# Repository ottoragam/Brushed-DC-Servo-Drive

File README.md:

# Brushed-DC-Servo-Drive
Low cost servo drive for small CNC machinery

##New version available on https://github.com/ottoragam/Tarocco

----------------------------------------------------------------------
Brushed DC Servo Drive (c) by Gino Magarotto

Brushed DC Servo Drive is licensed under a
Creative Commons Attribution-ShareAlike 3.0 Unported License.

You should have received a copy of the license along with this
work.  If not, see <http://creativecommons.org/licenses/by-sa/3.0/>.

----------------------------------------------------------------------
Low cost servo drive for small CNC machinery

Project log on https://hackaday.io/project/9433-brushed-dc-servo-drive

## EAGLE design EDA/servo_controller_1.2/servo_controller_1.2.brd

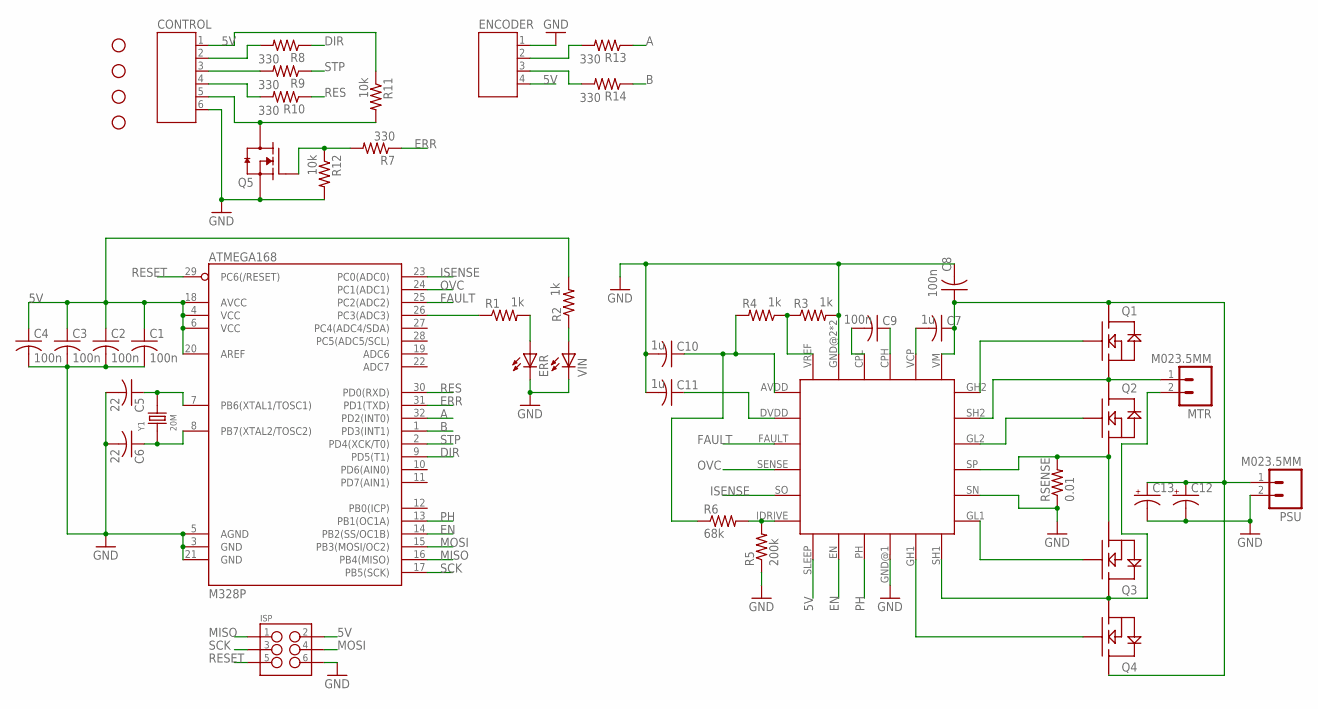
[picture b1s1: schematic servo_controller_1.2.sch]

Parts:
8701: DRV8701; VQFN24
C1, C2, C3, C4, C8, C9: 100n; C0603
C5, C6: 22; C0603
C7, C10, C11: 1u; C0603
C12, C13: CPOL-USE5-8.5; E5-8,5
CONTROL: JST-PH6
ENCODER: JST-PH4
ERR: LEDCHIP-LED0603; CHIP-LED0603
ISP: M03X22X3_SILK_SM; 2X3
M328P: ATMEGA168; TQFP32-08
MTR: M023.5MM; SCREWTERMINAL-3.5MM-2
PSU: M023.5MM; SCREWTERMINAL-3.5MM-2
Q1, Q2, Q3, Q4: NEXFET_SINGLECSD18537NQ5A; SON5X6
Q5: MOSFET-NCH_SOT-23; SOT95P280X135-3N
R1, R2, R3, R4: 1k; R0603
R5: 200k; R0603
R6: 68k; R0603
R7, R8, R9, R10, R13, R14: 330; R0603
R11, R12: 10k; R0603
RSENSE: 0.01; R2512
STANDOFF1, STANDOFF2, STANDOFF3, STANDOFF4: STAND-OFF
VIN: LEDCHIP-LED0603; CHIP-LED0603
Y1: 20M; X2-SMD-5.0X3.2X1.3MM

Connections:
5V: 8701.SLEEP, C1.1, C2.1, C3.1, C4.1, CONTROL.1, ENCODER.4, ISP.2, M328P.4 (VCC), M328P.6 (VCC), M328P.18 (AVCC), M328P.20 (AREF), R2.2, R11.1
A: M328P.32 (PD2(INT0)), R13.1
B: M328P.1 (PD3(INT1)), R14.1
DIR: M328P.9 (PD5(T1)), R8.1
EN: 8701.EN, M328P.14 (PB2(SS/OC1B))
ERR: M328P.31 (PD1(TXD)), R7.1
FAULT: 8701.FAULT, M328P.25 (PC2(ADC2))
GND: 8701.GND@1 (GND), 8701.GND@2 (GND), 8701.GND@3 (GND), 8701.SN, C1.2, C2.2, C3.2, C4.2, C5.2, C6.2, C8.2, C10.2, C11.2, C12.-, C13.-, CONTROL.6, ENCODER.1, ERR.C, ISP.6, M328P.3 (GND), M328P.5 (AGND), M328P.21 (GND), PSU.2, Q5.2 (S), R3.2, R5.1, R12.2, RSENSE.1, VIN.C
ISENSE: 8701.SO, M328P.23 (PC0(ADC0))
MISO: ISP.1, M328P.16 (PB4(MISO))
MOSI: ISP.4, M328P.15 (PB3(MOSI/OC2))
unnamed: 8701.GL1, Q3.GATE
unnamed: 8701.SH1, MTR.2, Q3.DRAIN@1 (DRAIN), Q3.DRAIN@2 (DRAIN), Q3.DRAIN@3 (DRAIN), Q3.DRAIN@4 (DRAIN), Q3.DRAIN@5 (DRAIN), Q4.SOURCE@1 (SOURCE), Q4.SOURCE@2 (SOURCE), Q4.SOURCE@3 (SOURCE)
unnamed: 8701.SH2, MTR.1, Q1.SOURCE@1 (SOURCE), Q1.SOURCE@2 (SOURCE), Q1.SOURCE@3 (SOURCE), Q2.DRAIN@1 (DRAIN), Q2.DRAIN@2 (DRAIN), Q2.DRAIN@3 (DRAIN), Q2.DRAIN@4 (DRAIN), Q2.DRAIN@5 (DRAIN)
unnamed: 8701.GH2, Q1.GATE
unnamed: 8701.SP, Q2.SOURCE@1 (SOURCE), Q2.SOURCE@2 (SOURCE), Q2.SOURCE@3 (SOURCE), Q3.SOURCE@1 (SOURCE), Q3.SOURCE@2 (SOURCE), Q3.SOURCE@3 (SOURCE), RSENSE.2
unnamed: 8701.GL2, Q2.GATE
unnamed: 8701.GH1, Q4.GATE
unnamed: R2.1, VIN.A
unnamed: C5.1, M328P.7 (PB6(XTAL1/TOSC1)), Y1.2
unnamed: ENCODER.2, R13.2
unnamed: 8701.VCP, C7.2
unnamed: 8701.CPL, C9.2
unnamed: 8701.CPH, C9.1
unnamed: ENCODER.3, R14.2
unnamed: 8701.VREF, R3.1, R4.1
unnamed: 8701.AVDD, C10.1, R4.2, R6.1
unnamed: 8701.DVDD, C11.1
unnamed: C6.1, M328P.8 (PB7(XTAL2/TOSC2)), Y1.1
unnamed: ERR.A, R1.2
unnamed: Q5.1 (G), R7.2, R12.1
unnamed: 8701.IDRIVE, R5.2, R6.2
unnamed: 8701.VM, C7.1, C8.1, C12.+, C13.+, PSU.1, Q1.DRAIN@1 (DRAIN), Q1.DRAIN@2 (DRAIN), Q1.DRAIN@3 (DRAIN), Q1.DRAIN@4 (DRAIN), Q1.DRAIN@5 (DRAIN), Q4.DRAIN@1 (DRAIN), Q4.DRAIN@2 (DRAIN), Q4.DRAIN@3 (DRAIN), Q4.DRAIN@4 (DRAIN), Q4.DRAIN@5 (DRAIN)
unnamed: M328P.26 (PC3(ADC3)), R1.1
unnamed: CONTROL.2, R8.2
unnamed: CONTROL.3, R9.2
unnamed: CONTROL.4, R10.2
unnamed: CONTROL.5, Q5.3 (D), R11.2
OVC: 8701.SENSE, M328P.24 (PC1(ADC1))
PH: 8701.PH, M328P.13 (PB1(OC1A))
RES: M328P.30 (PD0(RXD)), R10.1
RESET: ISP.5, M328P.29 (PC6(/RESET))
SCK: ISP.3, M328P.17 (PB5(SCK))
STP: M328P.2 (PD4(XCK/T0)), R9.1

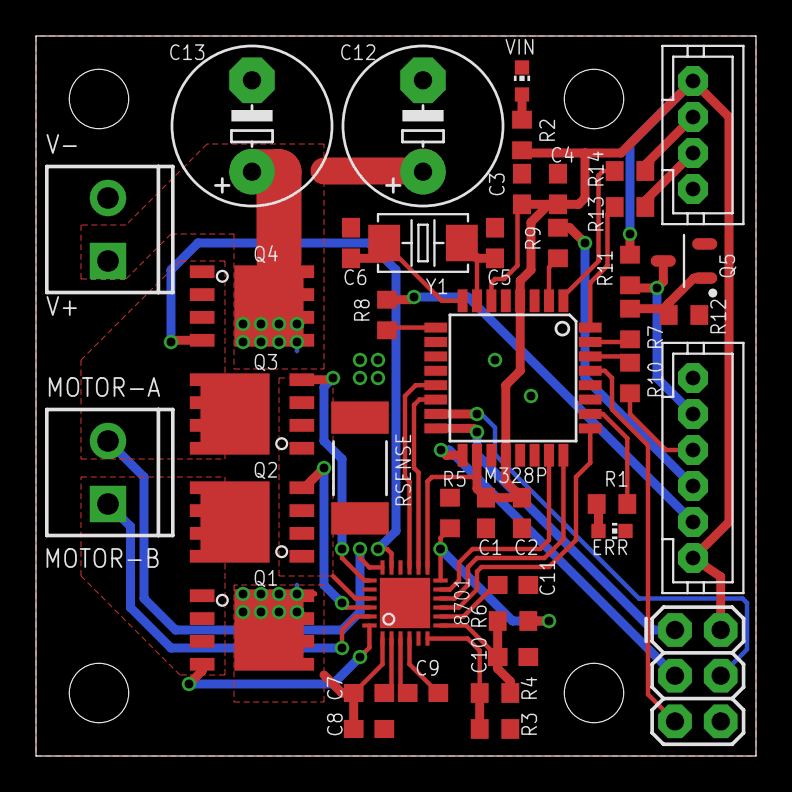
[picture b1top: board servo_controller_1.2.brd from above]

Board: 2 copper layers, 40.0 x 40.0 mm, 47 parts (0 on the bottom side), 44 nets.

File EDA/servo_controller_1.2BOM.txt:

Partlist exported from D:/diseño/PCB/boards/servo_controller_1.2/servo_controller_1.2.sch at 12/10/2015 11:50 p.m.

Qty Value                     Device                                        Package               Parts                                      Description                          MPN          
2                             CPOL-USE5-8.5                                 E5-8,5                C12, C13                                   POLARIZED CAPACITOR, American symbol              
1                             JST-PH4                                       JST-PH4               ENCODER                                                                                      
1                             JST-PH6                                       JST-PH6               CONTROL                                                                                      
2                             LEDCHIP-LED0603                               CHIP-LED0603          ERR, VIN                                   LED                                               
1                             M03X22X3_SILK_SM                              2X3                   ISP                                        2x3 .1" header.                                   
1   0.01                      R-US_R2512                                    R2512                 RSENSE                                     RESISTOR, American symbol                         
8   100n                      C-USC0603                                     C0603                 C1, C2, C3, C4, C5, C6, C8, C9             CAPACITOR, American symbol                        
2   10k                       R-US_R0603                                    R0603                 R11, R12                                   RESISTOR, American symbol                         
4   1k                        R-US_R0603                                    R0603                 R1, R2, R3, R4                             RESISTOR, American symbol                         
3   1u                        C-USC0603                                     C0603                 C7, C10, C11                               CAPACITOR, American symbol                        
1   200k                      R-US_R0603                                    R0603                 R5                                         RESISTOR, American symbol                         
1   20M                       SMD-CRYSTAL-16MHZ-8PF-20PPM-40R(2P-5.0X3.2MM) X2-SMD-5.0X3.2X1.3MM  Y1                                         306010054                            X053201602002
6   330                       R-US_R0603                                    R0603                 R7, R8, R9, R10, R13, R14                  RESISTOR, American symbol                         
1   68k                       R-US_R0603                                    R0603                 R6                                         RESISTOR, American symbol                         
1   ATMEGA168                 ATMEGA168                                     TQFP32-08             M328P                                      Atmel 32-pin 8-bit micro, 16k flash.              
1   DRV8701                   DRV8701                                       VQFN24                8701                                                                                         
2   M023.5MM                  M023.5MM                                      SCREWTERMINAL-3.5MM-2 MTR, PSU                                   Standard 2-pin 0.1" header. Use with              
1   MOSFET-NCH_SOT-23         MOSFET-NCH_SOT-23                             SOT95P280X135-3N      Q5                                                                                           
4   NEXFET_SINGLECSD18537NQ5A NEXFET_SINGLECSD18537NQ5A                     SON5X6                Q1, Q2, Q3, Q4                                                                               
4   STAND-OFF                 STAND-OFF                                     STAND-OFF             STANDOFF1, STANDOFF2, STANDOFF3, STANDOFF4 #4 Stand Off

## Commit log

2016-02-01 Create LICE
2016-02-01 Rename LICE to LICENSE.txt
2016-02-01 Eagle files
2016-02-01 Pics
2016-02-01 Edit
2016-02-01 add manual
2016-02-01 add firmware
2016-02-19 removed incorrect BOM file
2016-02-26 added encoder fault detection
2016-07-24 pinout diagram for the board
2016-11-01 tarocco

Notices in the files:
parts and their libraries:
SparkFun-Aesthetics: Licensing: Creative Commons ShareAlike 4.0 International - https://creativecommons.org/licenses/by-sa/4.0
